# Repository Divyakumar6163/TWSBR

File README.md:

# Robofest 4.0 - Two Wheeled Self Balancing Robot

## Overview

This repository contains all the documentation, design files, and implementation details of a **Two-Wheeled Self-Balancing Robot** developed by students of **IIT Bhubaneswar** as part of **Robofest 4.0**.

The robot operates on the principle of an **inverted pendulum**, achieving dynamic stability using sensors, real-time data processing, and a PID control system. It combines **self-balancing** capabilities with **line-following** functionality, and features a **payload-carrying structure**.

## Table of Contents

* [Overview](#overview)
* [Robot Description](#robot-description)
* [Salient Features](#salient-features)
* [Mechanical Design](#mechanical-design)
* [Electronics and Control](#electronics-and-control)
* [Softwares Used](#softwares-used)
* [Block Diagrams](#block-diagrams)
* [Applications](#applications)
* [Team](#team)

## Robot Description

The robot uses two NEMA 23 stepper motors driven by a PID controller implemented on an **Arduino Nano**. An **MPU-6050** sensor detects the tilt and angular velocity. The robot balances itself by calculating real-time error values and adjusting motor outputs accordingly.

## Salient Features

* **Self-Balancing** using MPU-6050 and PID control
* **Payload capacity** of \~1kg
* **Line-following** using IR sensors
* **Adjustable height** using threaded rods
* **Symmetric aluminum frame** for better stability

## Mechanical Design

* 3-layer structure with aluminum plates (Top, Middle, Bottom)
* Fully threaded rods for height adjustment
* Custom motor mount flanges
* Center of gravity optimized for balance

## Electronics and Control

* **Microcontroller**: Arduino Nano
* **Sensors**: MPU-6050, IR Sensors
* **Actuators**: NEMA 23/17 Stepper Motors with TB6600/A4988 drivers
* **Protection**: Diodes, resistors, and capacitors for circuit stability

## Softwares Used

* **Arduino IDE**: PID logic, sensor reading, and motor control
* **SolidWorks**: CAD design of chassis
* **MATLAB**: PID tuning and simulation
* **KiCad & Fritzing**: PCB and circuit design
* **VS Code (Python + OpenCV)**: Code Editor
* **ANSYS**: Stress and vibration analysis

## Block Diagrams

#### Electronics Block Diagram

#### Flowchart

## Applications

* Autonomous delivery systems
* Line-following warehouse bots
* Educational robotics
* Assistive mobility devices
* Smart surveillance platforms

## Team

**Team Members:**

* Ayush Gupta
* Divya Kumar
* Jiya Chakraborty
* Rachit Jain
* Vivek Singh

**Mentor:** Dr. Satyanarayan Panigrahi, Associate Professor, School of Mechanical Sciences

**Institute:** Indian Institute of Technology, Bhubaneswar

For full details, refer to the [REPORT.pdf](Reports/3.%20Grand_Finale/REPORT_finale.pdf) in the repository.

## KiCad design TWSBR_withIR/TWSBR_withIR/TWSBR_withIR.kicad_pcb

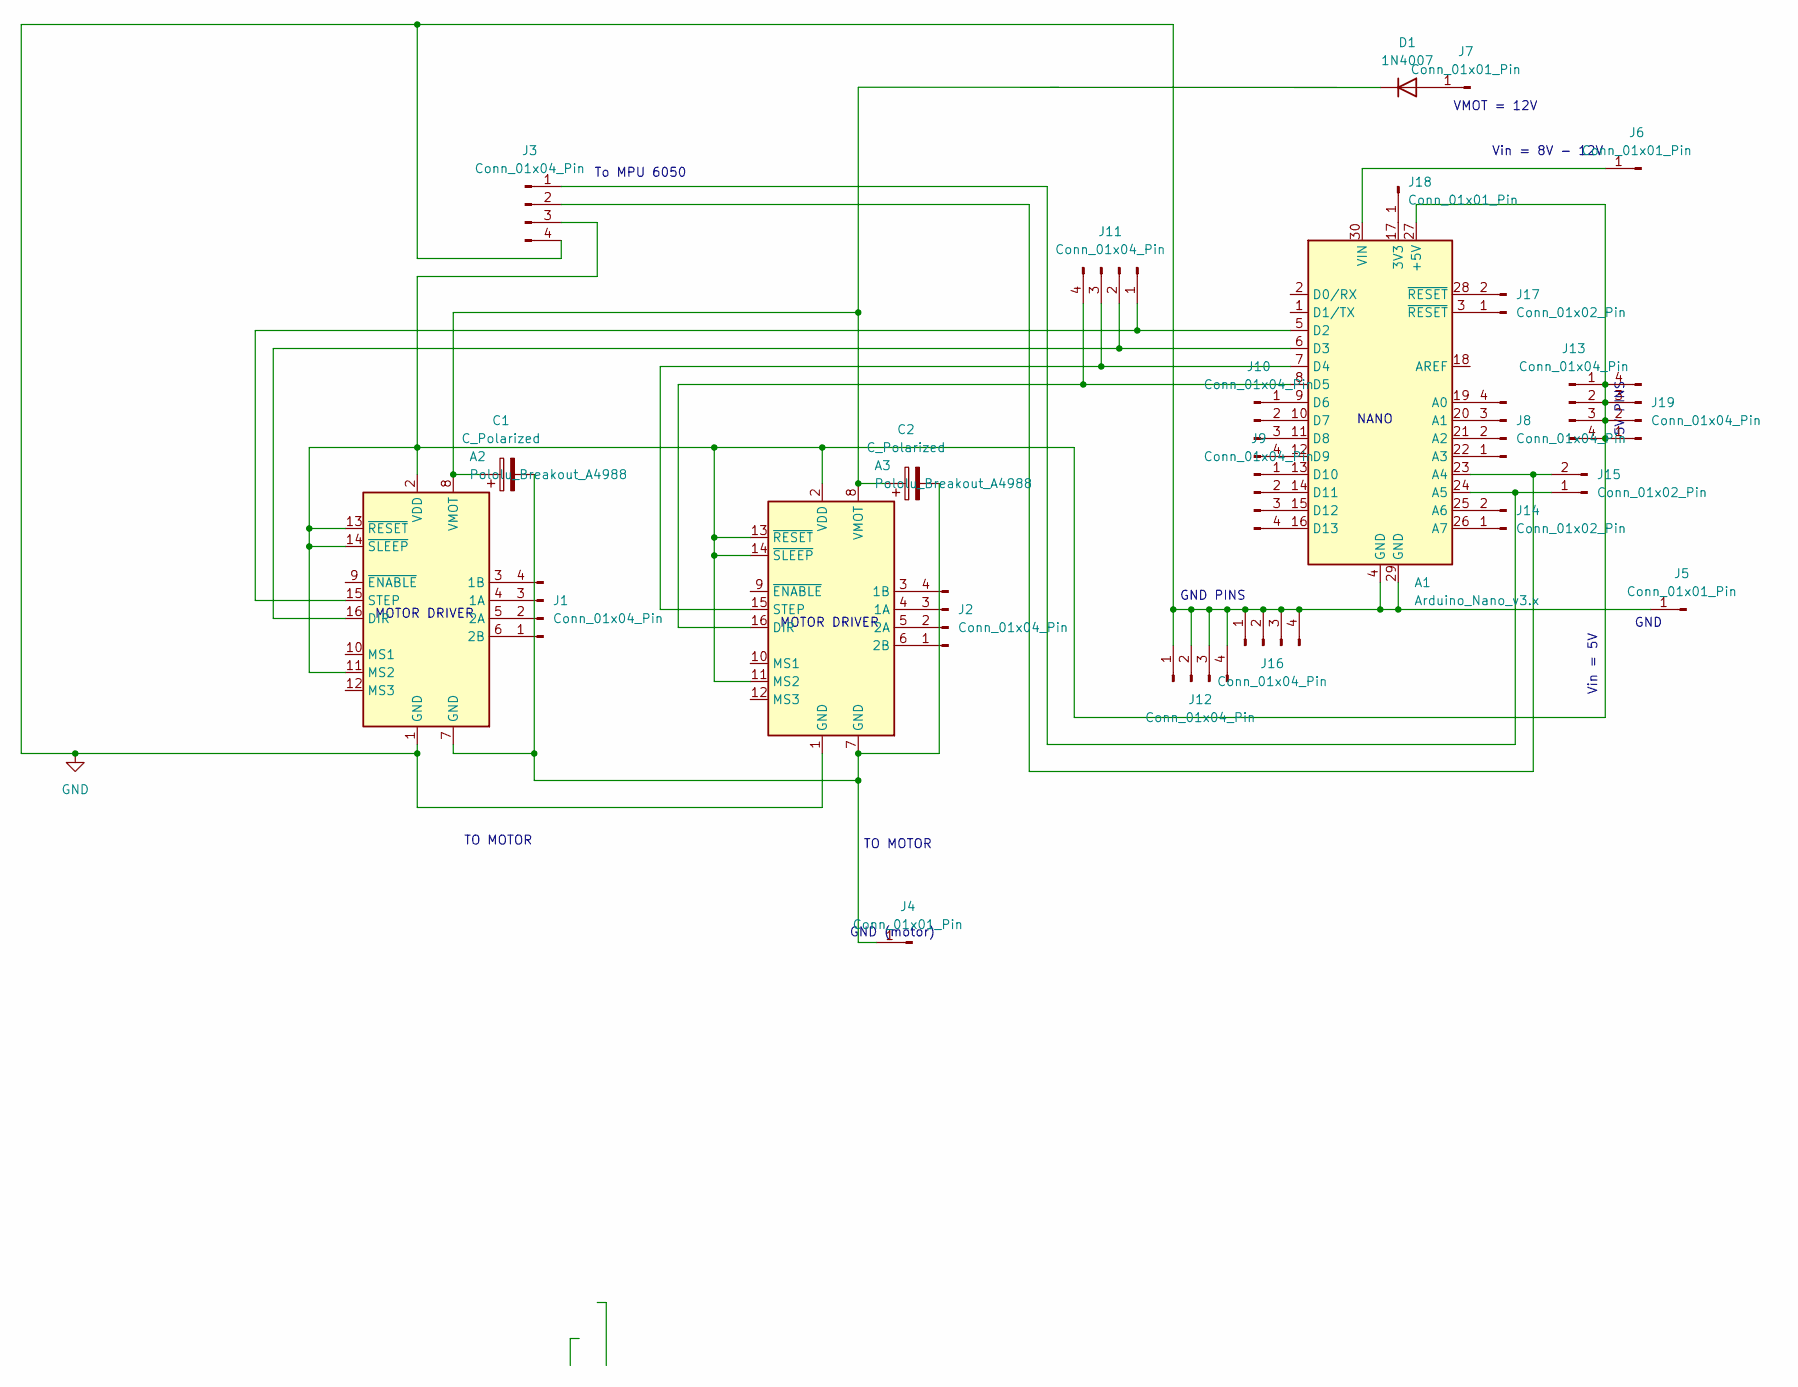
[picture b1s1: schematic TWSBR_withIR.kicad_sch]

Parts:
A1: Arduino_Nano_v3.x; Arduino_Nano
A2, A3: Pololu_Breakout_A4988; Pololu_Breakout-16_15.2x20.3mm
C1, C2: C_Polarized; LED_Rectangular_W5.0mm_H2.0mm_Horizontal_O1.27mm_Z3.0mm
D1: 1N4007; D_DO-41_SOD81_P10.16mm_Horizontal
J1, J2, J3, J8, J9, J10, J11, J12, J13, J16, J19: Conn_01x04_Pin; PinHeader_1x04_P1.00mm_Vertical
J4, J5, J6, J7, J18: Conn_01x01_Pin; PinHeader_1x01_P1.00mm_Vertical
J14, J15, J17: Conn_01x02_Pin; PinHeader_1x02_P1.00mm_Vertical

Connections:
GND: A1.4 (GND), A1.29 (GND), A2.1 (GND), A3.1 (GND), J3.4, J5.1, J12.1, J12.2, J12.3, J12.4, J16.1, J16.2, J16.3, J16.4
unnamed: A1.17 (3V3), J18.1
unnamed: A1.27 (+5V), A2.2 (VDD), A2.11 (MS2), A2.13 (~RESET), A2.14 (~SLEEP), A3.2 (VDD), A3.11 (MS2), A3.13 (~RESET), A3.14 (~SLEEP), J3.3, J13.1, J13.2, J13.3, J13.4, J19.1, J19.2, J19.3, J19.4
unnamed: A1.19 (A0), J8.4
unnamed: A1.20 (A1), J8.3
unnamed: A1.21 (A2), J8.2
unnamed: A1.22 (A3), J8.1
unnamed: A1.23 (A4), J3.2, J15.2
unnamed: A1.24 (A5), J3.1, J15.1
unnamed: A1.25 (A6), J14.2
unnamed: A1.26 (A7), J14.1
unnamed: A1.5 (D2), A2.15 (STEP), J11.1
unnamed: A1.6 (D3), A2.16 (DIR), J11.2
unnamed: A1.7 (D4), A3.15 (STEP), J11.3
unnamed: A1.8 (D5), A3.16 (DIR), J11.4
unnamed: A1.9 (D6), J10.1
unnamed: A1.10 (D7), J10.2
unnamed: A1.11 (D8), J10.3
unnamed: A1.12 (D9), J10.4
unnamed: A1.13 (D10), J9.1
unnamed: A1.14 (D11), J9.2
unnamed: A1.15 (D12), J9.3
unnamed: A1.16 (D13), J9.4
unnamed: A1.30 (VIN), J6.1
unnamed: A2.4 (1A), J1.3
unnamed: A2.3 (1B), J1.4
unnamed: A2.5 (2A), J1.2
unnamed: A2.6 (2B), J1.1
unnamed: A2.8 (VMOT), A3.8 (VMOT), C1.1, C2.1, D1.1 (K)
unnamed: A3.4 (1A), J2.3
unnamed: A3.3 (1B), J2.4
unnamed: A3.5 (2A), J2.2
unnamed: A3.6 (2B), J2.1
unnamed: D1.2 (A), J7.1
unnamed: A2.7 (GND), A3.7 (GND), C1.2, C2.2, J4.1
unnamed: A1.3 (~RESET), J17.1
unnamed: A1.28 (~RESET), J17.2

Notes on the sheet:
TO MOTOR
GND (motor)
MOTOR DRIVER
Vin = 8V - 12V
To MPU 6050
Vin = 5V
NANO
GND
5V PINS
GND PINS
VMOT = 12V

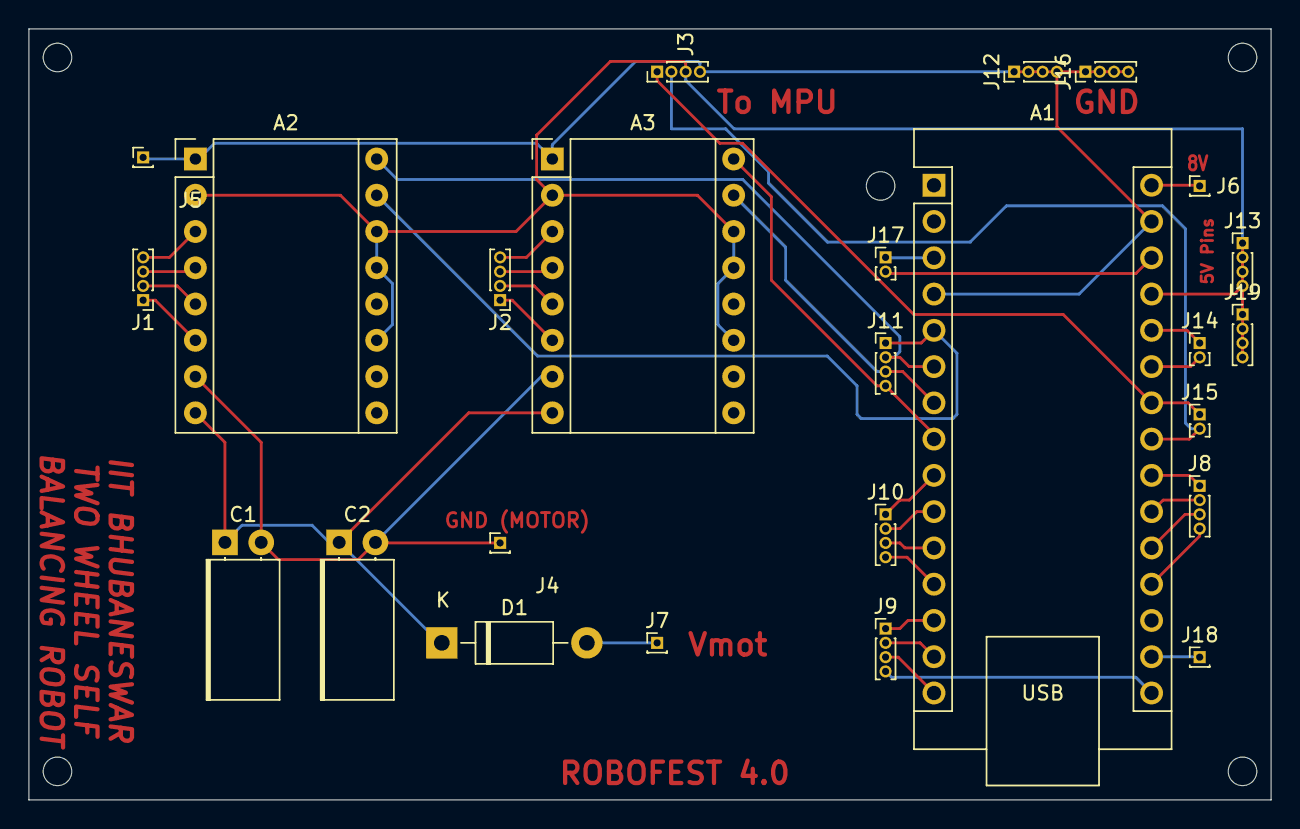
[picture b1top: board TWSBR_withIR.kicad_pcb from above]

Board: 2 copper layers, 87.0 x 54.0 mm, 25 parts (0 on the bottom side), 37 nets.

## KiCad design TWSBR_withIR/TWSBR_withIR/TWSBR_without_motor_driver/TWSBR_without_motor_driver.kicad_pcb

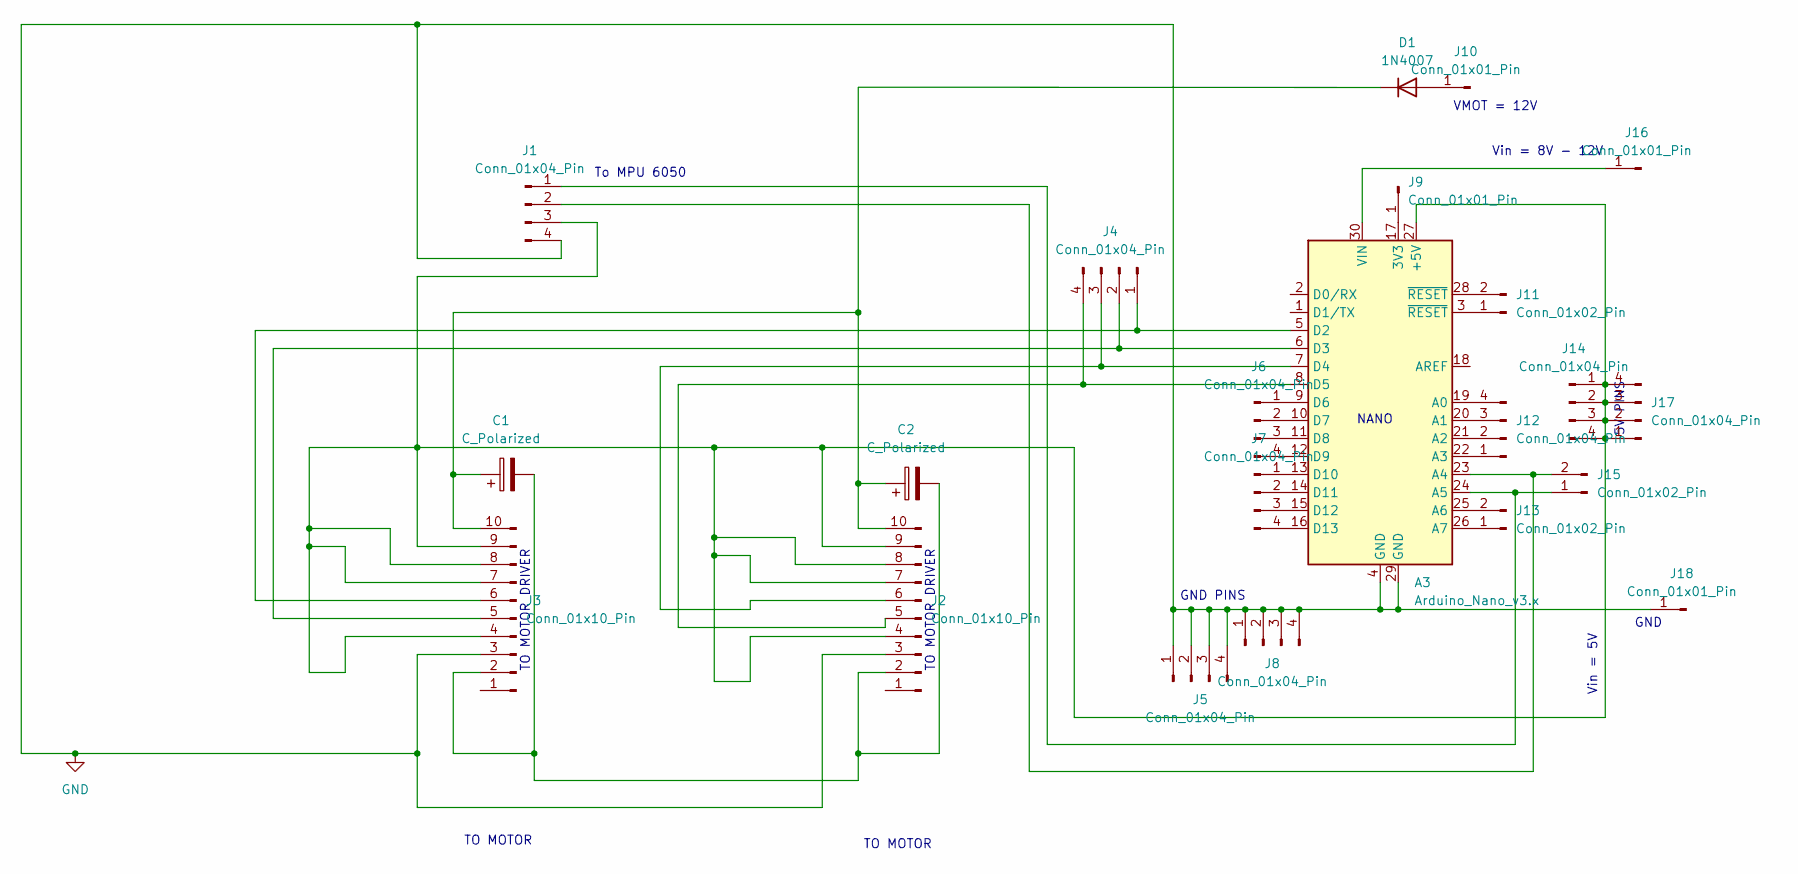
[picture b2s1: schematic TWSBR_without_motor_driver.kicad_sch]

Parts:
A3: Arduino_Nano_v3.x; Arduino_Nano
C1, C2: C_Polarized; LED_Rectangular_W5.0mm_H2.0mm_Horizontal_O1.27mm_Z3.0mm
D1: 1N4007; D_DO-41_SOD81_P10.16mm_Horizontal
J1, J4, J5, J6, J7, J8, J12, J14, J17: Conn_01x04_Pin; PinHeader_1x04_P1.00mm_Vertical
J2, J3: Conn_01x10_Pin; PinHeader_1x10_P1.00mm_Vertical
J9, J10, J16, J18: Conn_01x01_Pin; PinHeader_1x01_P1.00mm_Vertical
J11, J13, J15: Conn_01x02_Pin; PinHeader_1x02_P1.00mm_Vertical

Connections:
GND: A3.4 (GND), A3.29 (GND), J1.4, J2.3, J3.3, J5.1, J5.2, J5.3, J5.4, J8.1, J8.2, J8.3, J8.4, J18.1
unnamed: A3.17 (3V3), J9.1
unnamed: A3.27 (+5V), J1.3, J2.4, J2.7, J2.8, J2.9, J3.4, J3.7, J3.8, J3.9, J14.1, J14.2, J14.3, J14.4, J17.1, J17.2, J17.3, J17.4
unnamed: A3.19 (A0), J12.4
unnamed: A3.20 (A1), J12.3
unnamed: A3.21 (A2), J12.2
unnamed: A3.22 (A3), J12.1
unnamed: A3.23 (A4), J1.2, J15.2
unnamed: A3.24 (A5), J1.1, J15.1
unnamed: A3.25 (A6), J13.2
unnamed: A3.26 (A7), J13.1
unnamed: A3.5 (D2), J3.6, J4.1
unnamed: A3.6 (D3), J3.5, J4.2
unnamed: A3.7 (D4), J2.6, J4.3
unnamed: A3.8 (D5), J2.5, J4.4
unnamed: A3.9 (D6), J6.1
unnamed: A3.10 (D7), J6.2
unnamed: A3.11 (D8), J6.3
unnamed: A3.12 (D9), J6.4
unnamed: A3.13 (D10), J7.1
unnamed: A3.14 (D11), J7.2
unnamed: A3.15 (D12), J7.3
unnamed: A3.16 (D13), J7.4
unnamed: A3.30 (VIN), J16.1
unnamed: D1.2 (A), J10.1
unnamed: C1.1, C2.1, D1.1 (K), J2.10, J3.10
unnamed: C1.2, C2.2, J2.2, J3.2
unnamed: A3.3 (~RESET), J11.1
unnamed: A3.28 (~RESET), J11.2

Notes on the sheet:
5V PINS
TO MOTOR
TO MOTOR DRIVER
VMOT = 12V
Vin = 5V
GND PINS
GND
NANO
Vin = 8V - 12V
TO MOTOR DRIVER
To MPU 6050

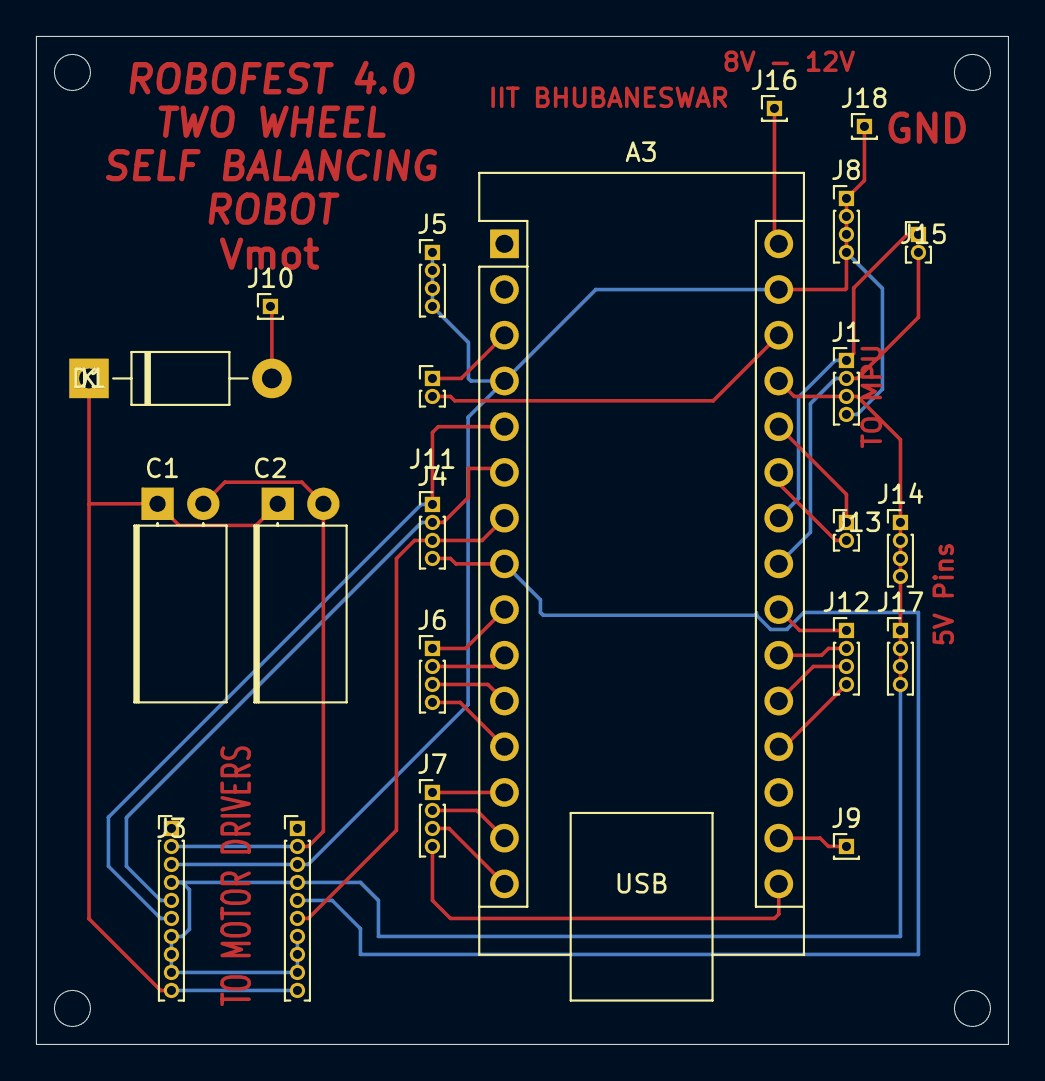
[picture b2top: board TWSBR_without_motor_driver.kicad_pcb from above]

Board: 2 copper layers, 54.0 x 56.0 mm, 22 parts (0 on the bottom side), 29 nets.

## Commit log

2024-04-21 Model Completed
2024-04-21 bearing added
2024-04-28 updated file structure
2024-06-12 Report added
2024-06-25 ESP 32 Added
2024-06-30 Report updated
2024-09-20 add: test codes
2024-09-25 Update in pid code
2024-09-29 CAD Update
2024-10-01 code thoda thoda chl rha
    torque pura aa rha but balance ni ho rha abhi
2024-10-02 if Tx in esp8266 is LOW, debugMode is ON
2024-10-05 updated code
2024-10-13 working code updated with remote controller
2024-10-13 Code and file Added
2024-10-15 Final CAD Updated
2024-10-15 POC Doc added
2024-10-20 added code for sir ka circuit and our circuit
2024-10-23 few changes
2024-10-25 trial#2
2024-10-27 final poc code
2024-12-21 Aluminum Model added
2025-01-05 add line following code
2025-01-05 Created takeImages.py
2025-01-06 Al model update
2025-01-20 code update chl rha
2025-01-20 PCB FILES
2025-01-21 final code
    robofest done and dusted
2025-02-07 Folder updates
2025-02-07 Unzip IR
2025-05-09 file updates
2025-05-10 Files added
